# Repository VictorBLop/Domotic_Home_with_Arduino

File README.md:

# Domotic_Home_with_Arduino
The project consists of a domotic home controlled both by Bluetooth via mobile application or by a keyboard in Arduino. The house includes both temperature and light sensors and a fan to make the temperature decrease. 

The documents are the next ones:
- "..ino" The code in Arduino.
- "..pptx" The presentation of the project to the professor.

MADE during Erasmus in Naples, Italy.

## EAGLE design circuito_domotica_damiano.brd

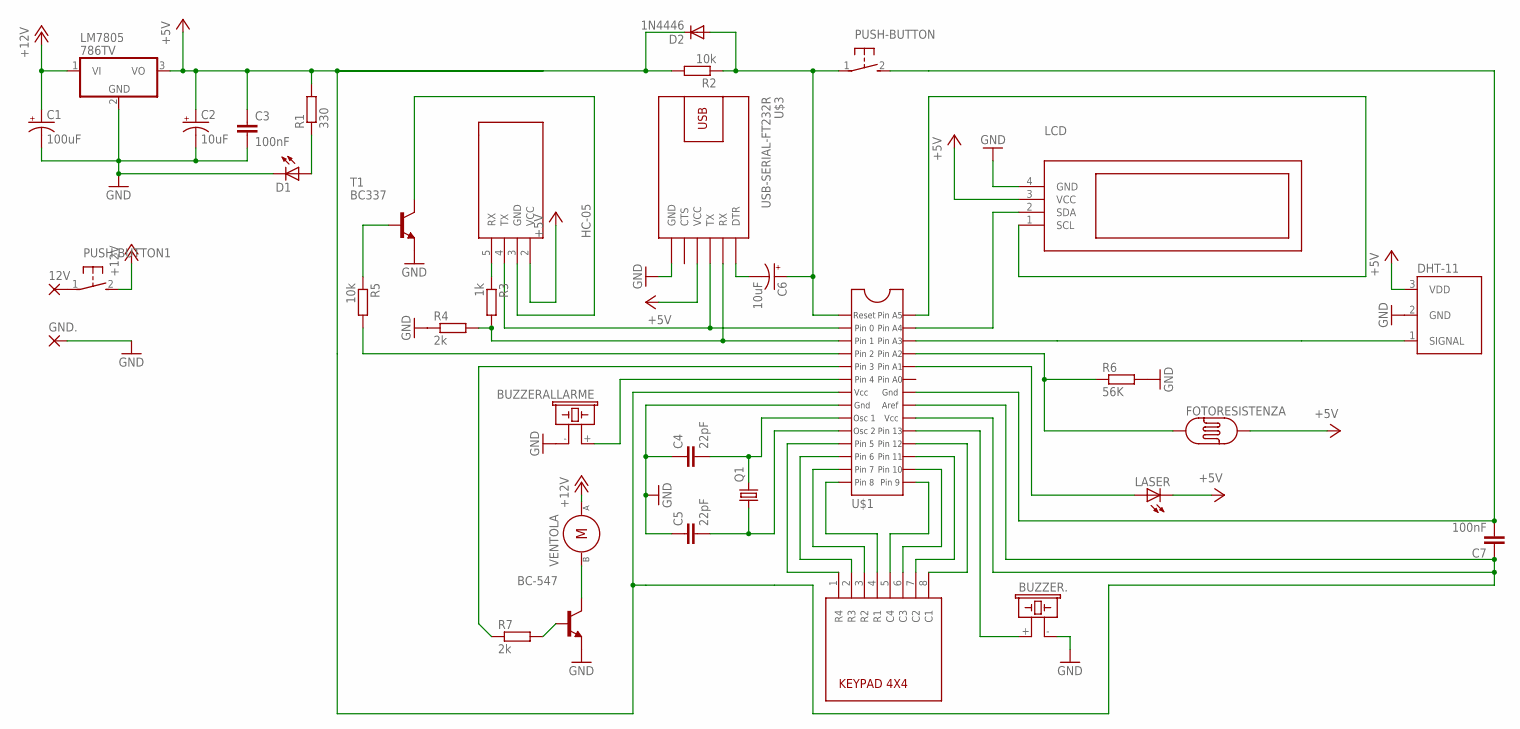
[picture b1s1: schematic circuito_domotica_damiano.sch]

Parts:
12V: WIREPAD1,6/0,8; 1,6/0,8
BC-547: BC547-NPN-TO92-CBE; TO92-CBE
BUZZER.: BPT-24X
BUZZERALLARME: BPT-24X
C1: 100uF; E2,5-6E
C2, C6: 10uF; E2,5-6E
C3, C7: 100nF; C025-030X050
C4, C5: 22pF; C025-030X050
D1: SFH482
D2: 1N4446; DO35-10
DHT-11: DS18B20; TO-92-AMMO
FOTORESISTENZA: PHOTOCELLPTH; PHOTOCELL
GND.: WIREPAD1,6/0,8; 1,6/0,8
HC-05: WIRELESS-BLUETOOTH-HC-05
LASER: SFH482
LCD: DISPLAY-OLED-128X32
LM7805: 786TV; TO220V
PUSH-BUTTON, PUSH-BUTTON1: DTS-3
Q1: CRYSTALHC49S; HC49/S
R1: 330; 0207/10
R2, R5: 10k; 0207/10
R3: 1k; 0207/10
R4, R7: 2k; 0207/10
R6: 56K; 0207/10
T1: BC337; TO92
U$1: DEVU; PACU
U$2: KEYPAD4X4
U$3: USB-SERIAL-FT232R
VENTOLA: DEVU4; PACU4

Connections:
+5V: C2.+, C3.1, C7.1, D2.C, DHT-11.3 (VDD), FOTORESISTENZA.2, HC-05.2 (VCC), LASER.K (C), LCD.3 (VCC), LM7805.3 (VO), R1.2, R2.2, U$1.7 (VCC), U$1.20 (VCC1), U$1.21 (AREF), U$3.4 (VCC)
+12V: C1.+, LM7805.1 (VI), PUSH-BUTTON1.2, VENTOLA.P$1
GND: BC-547.E, BUZZER..- (2), BUZZERALLARME.- (2), C1.-, C2.-, C3.2, C4.1, C5.1, D1.K (C), DHT-11.2 (GND), GND..1, LCD.4 (GND), LM7805.2 (GND), R4.1, R6.2, T1.1 (E), U$1.8 (GND), U$3.6 (GND)
unnamed: LCD.2 (SDA), U$1.27 (PINA4)
unnamed: DHT-11.1 (SIGNAL), U$1.26 (PINA3)
unnamed: C6.+, D2.A, PUSH-BUTTON.1, R2.1, U$1.1 (RESET)
unnamed: HC-05.3 (GND), T1.3 (C)
unnamed: FOTORESISTENZA.1, R6.1, U$1.25 (PINA2)
unnamed: C4.2, Q1.2, U$1.9 (X1)
unnamed: C5.2, Q1.1, U$1.10 (X2)
unnamed: LASER.A, U$1.24 (PINA1)
unnamed: C7.2, PUSH-BUTTON.2, U$1.22 (GND1)
unnamed: 12V.1, PUSH-BUTTON1.1
unnamed: R5.1, T1.2 (B)
unnamed: BUZZERALLARME.+ (1), U$1.6 (PIN4)
unnamed: R5.2, U$1.4 (PIN2)
unnamed: LCD.1 (SCL), U$1.28 (PINA5)
unnamed: C6.-, U$3.1 (DTR)
unnamed: BUZZER..+ (1), U$1.19 (PIN13)
unnamed: U$1.18 (PIN12), U$2.8 (C1)
unnamed: U$1.17 (PIN11), U$2.7 (C2)
unnamed: U$1.16 (PIN10), U$2.6 (C3)
unnamed: U$1.15 (PIN9), U$2.5 (C4)
unnamed: BC-547.C, VENTOLA.P$2
unnamed: U$1.14 (PIN8), U$2.4 (R1)
unnamed: U$1.13 (PIN7), U$2.3 (R2)
unnamed: U$1.12 (PIN6), U$2.2 (R3)
unnamed: BC-547.B, R7.2
unnamed: D1.A, R1.1
unnamed: U$1.11 (PIN5), U$2.1 (R4)
unnamed: R7.1, U$1.5 (PIN3)
unnamed: HC-05.4 (TX), U$1.2 (PIN0), U$3.3 (TX)
unnamed: HC-05.5 (RX), R3.1
unnamed: R3.2, R4.2, U$1.3 (PIN1), U$3.2 (RX)

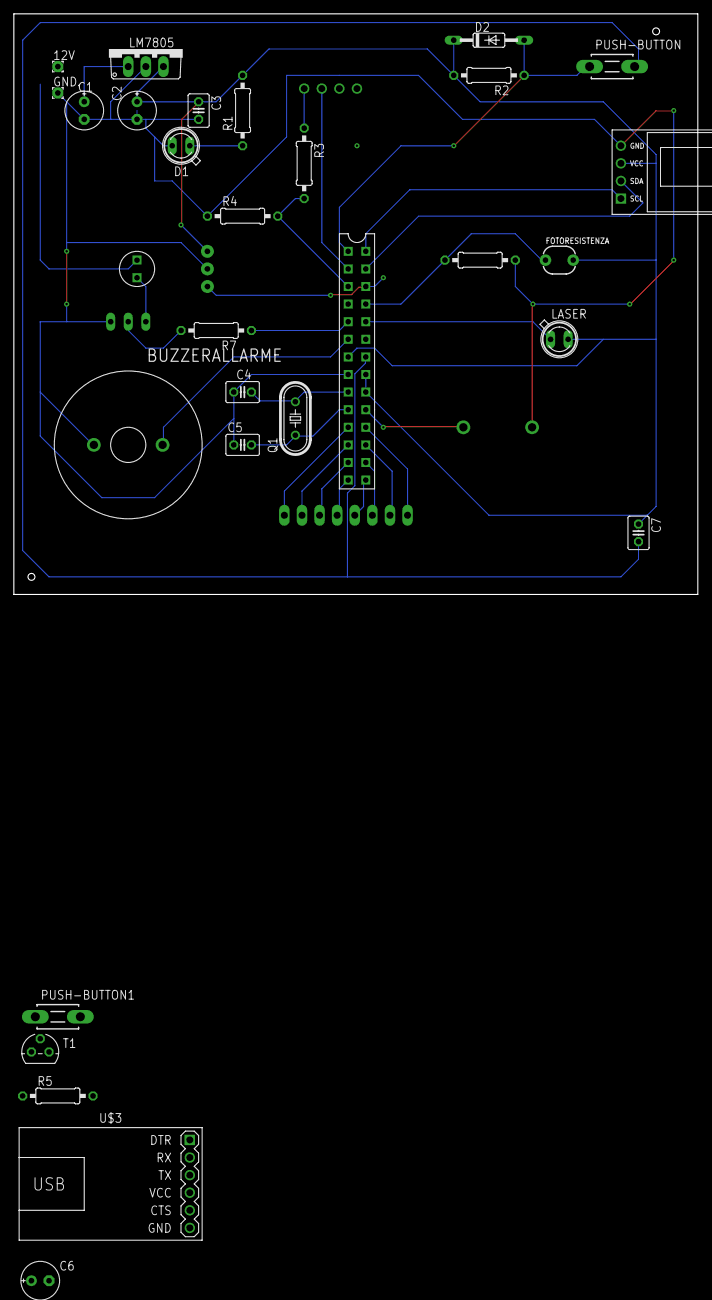
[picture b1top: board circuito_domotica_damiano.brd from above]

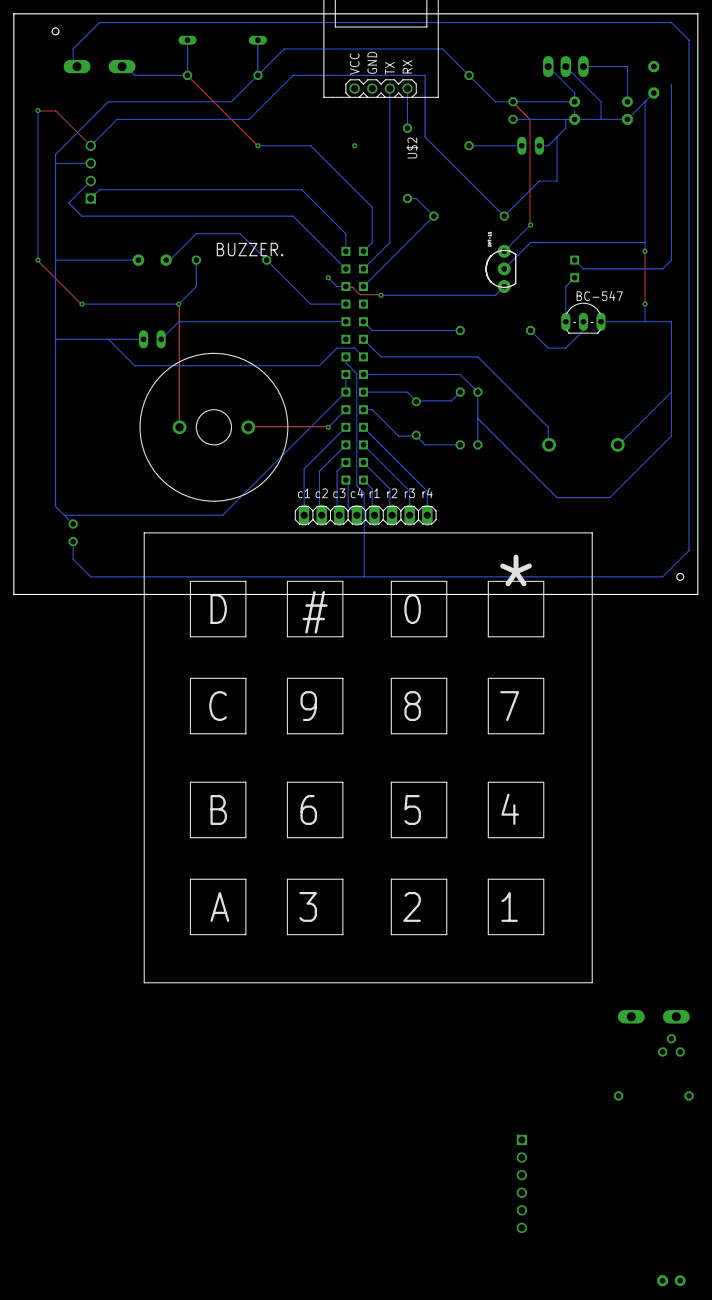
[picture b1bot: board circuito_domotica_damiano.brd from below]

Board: 2 copper layers, 98.7 x 83.8 mm, 35 parts (5 on the bottom side), 34 nets.

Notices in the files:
parts and their libraries:
SparkFun-Sensors: Licensing: Creative Commons ShareAlike 4.0 International - https://creativecommons.org/licenses/by-sa/4.0
diy-modules: Released under the Creative Commons Attribution 4.0 International License: http://creativecommons.org/licenses/by/4.0
